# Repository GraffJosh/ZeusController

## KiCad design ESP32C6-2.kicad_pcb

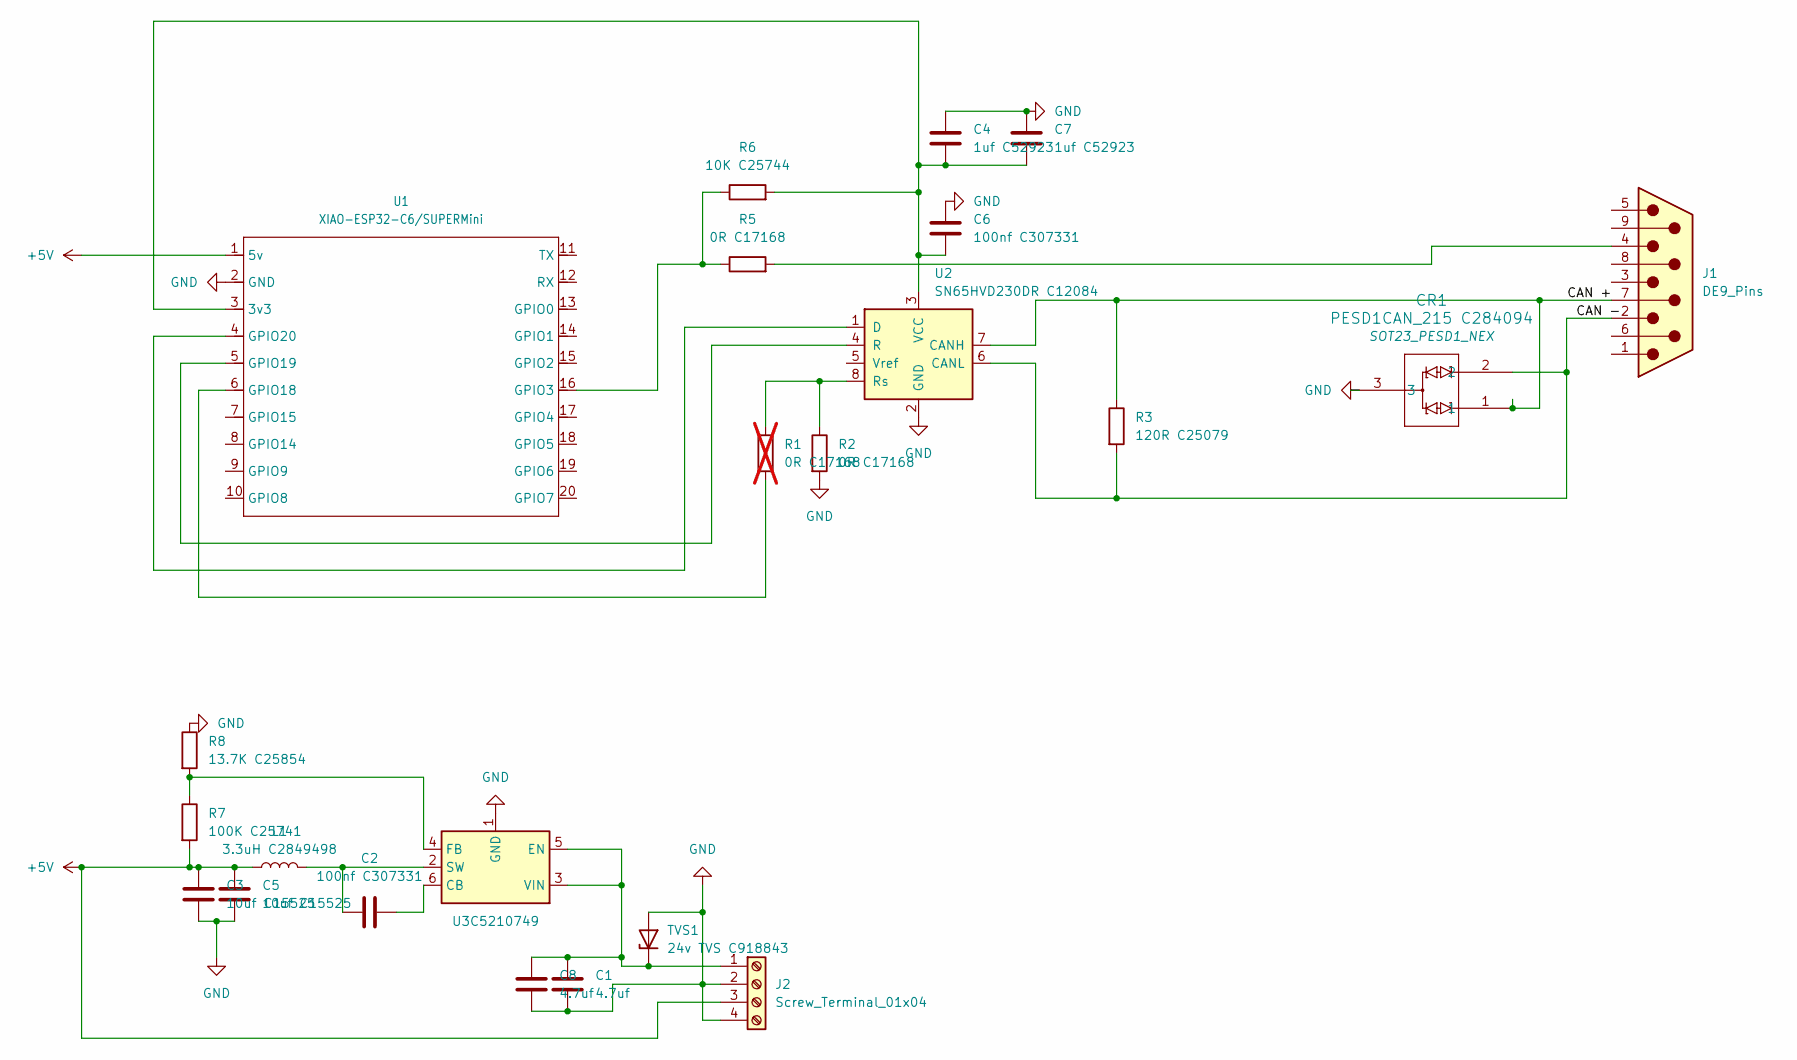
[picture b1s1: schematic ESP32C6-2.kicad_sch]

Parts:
C1, C8: 4.7uf; C_0402_1005Metric_Pad0.74x0.62mm_HandSolder
C2, C6: 100nf C307331; C_0402_1005Metric_Pad0.74x0.62mm_HandSolder
C3, C5: 10uf C15525; C_0402_1005Metric_Pad0.74x0.62mm_HandSolder
C4, C7: 1uf C52923; C_0402_1005Metric_Pad0.74x0.62mm_HandSolder
CR1: PESD1CAN_215 C284094; SOT23_PESD1_NEX
J1: DE9_Pins; DSUB-9_Pins_Vertical_P2.77x2.84mm_MountingHoles
J2: Screw_Terminal_01x04; TerminalBlock_Phoenix_MPT-0,5-4-2.54_1x04_P2.54mm_Horizontal
L1: 3.3uH C2849498; L_APV_ANR5040
R1: 0R C17168; R_0402_1005Metric; not fitted
R2, R5: 0R C17168; R_0402_1005Metric
R3: 120R C25079; R_0402_1005Metric
R6: 10K C25744; R_0402_1005Metric
R7: 100K C25741; R_0402_1005Metric
R8: 13.7K C25854; R_0402_1005Metric
TVS1: 24v TVS C918843; TVS SOD-123FL_L3.0-W1.8-LS3.7-RD C918843
U1: XIAO-ESP32-C6/SUPERMini; SUPERMINI-ESP32C6-DIP
U2: SN65HVD230DR C12084; SOIC-8_3.9x4.9mm_P1.27mm
U3C5210749: LMR51430YDDCR; SOT-23-6

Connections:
+5V: C3.1, C5.1, J2.3, L1.1, R7.2, U1.1 (5v)
/CAN +: CR1.1, J1.7, R3.1, U2.7 (CANH)
/CAN -: CR1.2, J1.2, R3.2, U2.6 (CANL)
GND: C1.1, C3.2, C4.1, C5.2, C6.1, C7.1, C8.1, CR1.3, J2.2, J2.4, R2.2, R8.1, TVS1.2 (A), U1.2 (GND), U2.2 (GND), U3C5210749.1 (GND)
unnamed: J1.4, R5.2
unnamed: C1.2, C8.2, J2.1, TVS1.1 (K), U3C5210749.3 (VIN), U3C5210749.5 (EN)
unnamed: C4.2, C6.2, C7.2, R6.2, U1.3 (3v3), U2.3 (VCC)
unnamed: R5.1, R6.1, U1.16 (GPIO3)
unnamed: R1.2, U1.6 (GPIO18)
unnamed: U1.5 (GPIO19), U2.4 (R)
unnamed: U1.4 (GPIO20), U2.1 (D)
unnamed: R1.1, R2.1, U2.8 (Rs)
unnamed: C2.2, U3C5210749.6 (CB)
unnamed: R7.1, R8.2, U3C5210749.4 (FB)
unnamed: C2.1, L1.2, U3C5210749.2 (SW)

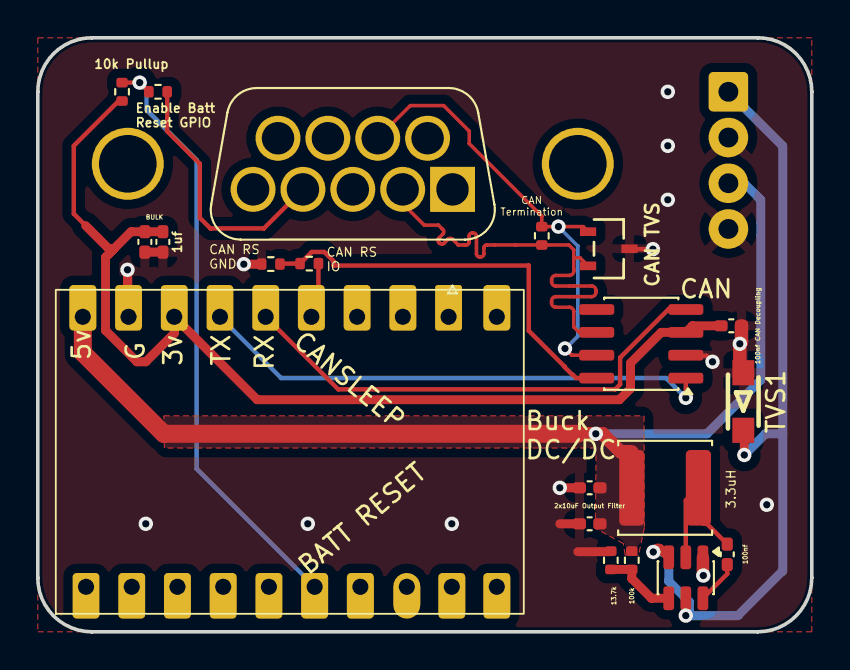
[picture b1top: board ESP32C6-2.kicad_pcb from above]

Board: 2 copper layers, 43.0 x 33.0 mm, 21 parts (1 on the bottom side), 15 nets.

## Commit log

2025-11-24 First Pass
2025-12-02 Update to add TVS and ground plane
2025-12-13 Rev 1, as built
